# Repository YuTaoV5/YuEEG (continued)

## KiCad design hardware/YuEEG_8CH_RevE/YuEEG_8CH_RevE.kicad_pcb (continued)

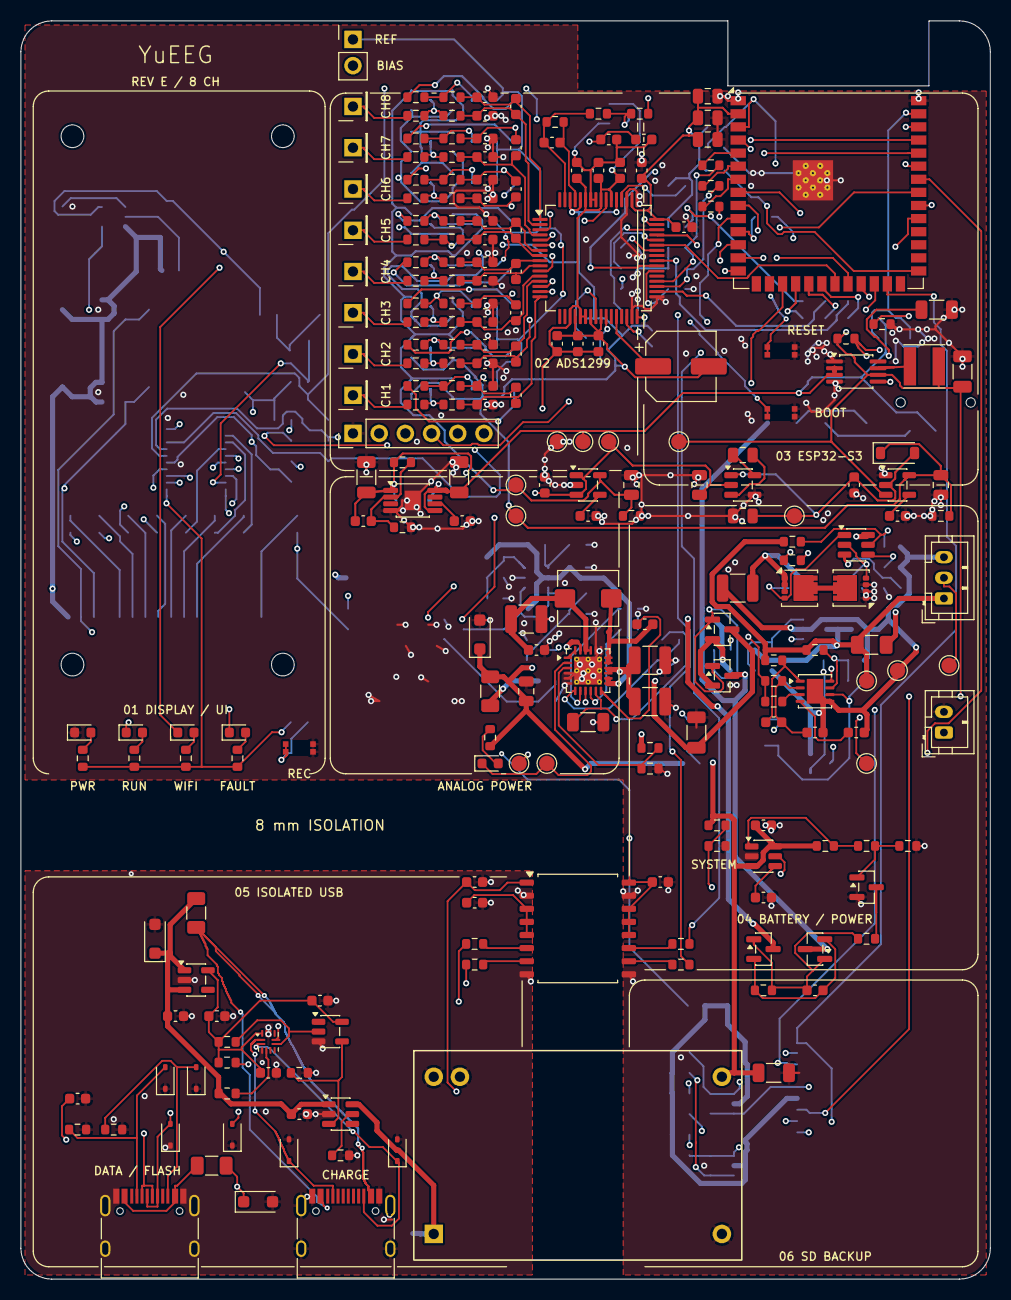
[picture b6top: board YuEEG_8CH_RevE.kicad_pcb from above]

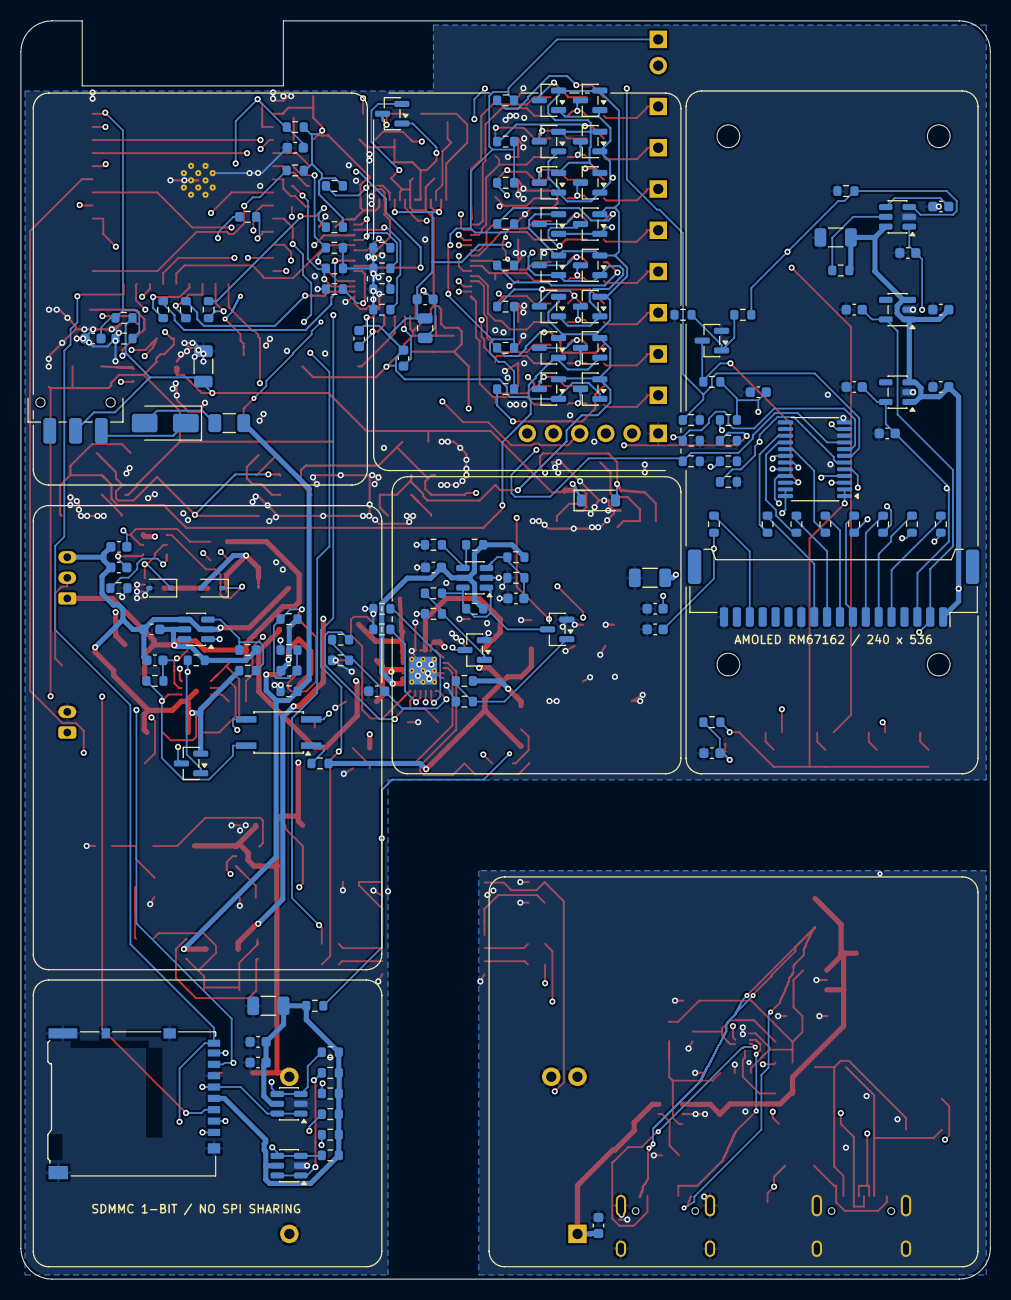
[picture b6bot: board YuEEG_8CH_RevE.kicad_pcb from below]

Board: 4 copper layers, 94.0 x 122.0 mm, 378 parts (145 on the bottom side), 224 nets.

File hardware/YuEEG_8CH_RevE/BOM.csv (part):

Reference,Value,Footprint,Sheet,Datasheet
U1,ADS1299PAG,Package_QFP:TQFP-64_10x10mm_P0.5mm,afe_core,https://www.ti.com/lit/ds/symlink/ads1299.pdf
R201,10k,Resistor_SMD:R_0603_1608Metric,afe_core,~
R202,10k,Resistor_SMD:R_0603_1608Metric,afe_core,~
R203,10k,Resistor_SMD:R_0603_1608Metric,afe_core,~
R204,10k,Resistor_SMD:R_0603_1608Metric,afe_core,~
R205,10k,Resistor_SMD:R_0603_1608Metric,afe_core,~
R206,10k,Resistor_SMD:R_0603_1608Metric,afe_core,~
R207,10k,Resistor_SMD:R_0603_1608Metric,afe_core,~
R208,10k,Resistor_SMD:R_0603_1608Metric,afe_core,~
R209,10k,Resistor_SMD:R_0603_1608Metric,afe_core,~
R210,1M 1%,Resistor_SMD:R_0603_1608Metric,afe_core,~
C201,1.5n C0G,Capacitor_SMD:C_0603_1608Metric,afe_core,~
R211,499k 1%,Resistor_SMD:R_0603_1608Metric,afe_core,~
R212,499k 1%,Resistor_SMD:R_0603_1608Metric,afe_core,~
J201,REF / BIAS,Connector_PinHeader_2.54mm:PinHeader_1x02_P2.54mm_Vertical,afe_core,~
C202,10u 10V X7R,Capacitor_SMD:C_0805_2012Metric,afe_core,~
C203,100n 10V,Capacitor_SMD:C_0603_1608Metric,afe_core,~
C210,1u 10V X7R,Capacitor_SMD:C_0603_1608Metric,afe_core,~
C211,1u 10V X7R,Capacitor_SMD:C_0603_1608Metric,afe_core,~
C212,1u 10V X7R,Capacitor_SMD:C_0603_1608Metric,afe_core,~
C213,1u 10V X7R,Capacitor_SMD:C_0603_1608Metric,afe_core,~
C214,1u 10V X7R,Capacitor_SMD:C_0603_1608Metric,afe_core,~
C215,1u 10V X7R,Capacitor_SMD:C_0603_1608Metric,afe_core,~
C216,1u 10V X7R,Capacitor_SMD:C_0603_1608Metric,afe_core,~
C217,1u 10V X7R,Capacitor_SMD:C_0603_1608Metric,afe_core,~
C220,100u 10V,Capacitor_SMD:CP_Elec_6.3x7.7,afe_core,~
C221,1u 10V,Capacitor_SMD:C_0603_1608Metric,afe_core,~
C222,1u 10V,Capacitor_SMD:C_0603_1608Metric,afe_core,~
C223,100n 10V,Capacitor_SMD:C_0603_1608Metric,afe_core,~
C224,1u 10V,Capacitor_SMD:C_0603_1608Metric,afe_core,~
D801,BAV199 BIAS CLAMP,Package_TO_SOT_SMD:SOT-23,afe_core,https://assets.nexperia.com/documents/data-sheet/BAV199.pdf
U1001,TPS22918DBVR AMOLED POWER,Package_TO_SOT_SMD:SOT-23-6,amoled_ui,https://www.ti.com/lit/ds/symlink/tps22918.pdf
R1001,100k,Resistor_SMD:R_0603_1608Metric,amoled_ui,~
C1001,1n 25V,Capacitor_SMD:C_0603_1608Metric,amoled_ui,~
R1003,1k,Resistor_SMD:R_0603_1608Metric,amoled_ui,~
C1002,22u 10V X7R,Capacitor_SMD:C_1206_3216Metric,amoled_ui,~
C1003,100n 10V,Capacitor_SMD:C_0603_1608Metric,amoled_ui,~
U1002,TPS7A2028PDBVR,Package_TO_SOT_SMD:SOT-23-5,amoled_ui,https://www.ti.com/lit/ds/symlink/tps7a20.pdf
C1004,1u 10V,Capacitor_SMD:C_0603_1608Metric,amoled_ui,~
C1005,4.7u 10V,Capacitor_SMD:C_0603_1608Metric,amoled_ui,~
U1003,TPS7A2018PDBVR,Package_TO_SOT_SMD:SOT-23-5,amoled_ui,https://www.ti.com/lit/ds/symlink/tps7a20.pdf
C1006,1u 10V,Capacitor_SMD:C_0603_1608Metric,amoled_ui,~
C1007,4.7u 10V,Capacitor_SMD:C_0603_1608Metric,amoled_ui,~
U1004,SN74AXC8T245PWR / 3V3 -> 1V8,Package_SO:TSSOP-24_4.4x7.8mm_P0.65mm,amoled_ui,https://www.ti.com/lit/ds/symlink/sn74axc8t245.pdf
C1008,100n 10V,Capacitor_SMD:C_0603_1608Metric,amoled_ui,~
C1009,100n 10V,Capacitor_SMD:C_0603_1608Metric,amoled_ui,~
Q1001,MMBT3904 OE ENABLE,Package_TO_SOT_SMD:SOT-23,amoled_ui,https://www.onsemi.com/pdf/datasheet/pzt3904-d.pdf
R1002,10k,Resistor_SMD:R_0603_1608Metric,amoled_ui,~
R1004,100k,Resistor_SMD:R_0603_1608Metric,amoled_ui,~
R1005,1M,Resistor_SMD:R_0603_1608Metric,amoled_ui,~
R1021,22R,Resistor_SMD:R_0603_1608Metric,amoled_ui,~
R1022,22R,Resistor_SMD:R_0603_1608Metric,amoled_ui,~
R1023,22R,Resistor_SMD:R_0603_1608Metric,amoled_ui,~
R1024,22R,Resistor_SMD:R_0603_1608Metric,amoled_ui,~
R1025,22R,Resistor_SMD:R_0603_1608Metric,amoled_ui,~
R1026,22R,Resistor_SMD:R_0603_1608Metric,amoled_ui,~
R1027,22R,Resistor_SMD:R_0603_1608Metric,amoled_ui,~
J1001,DO0200PFS12 18-PIN HARNESS,Connector_Molex:Molex_Panelmate_53780-1870_1x18-1MP_P1.25mm_Horizontal,amoled_ui,~
R1006,10k,Resistor_SMD:R_0603_1608Metric,amoled_ui,~
R1031,47k,Resistor_SMD:R_0603_1608Metric,amoled_ui,~
R1032,47k,Resistor_SMD:R_0603_1608Metric,amoled_ui,~
R1033,47k,Resistor_SMD:R_0603_1608Metric,amoled_ui,~
R1034,47k,Resistor_SMD:R_0603_1608Metric,amoled_ui,~
R1035,47k,Resistor_SMD:R_0603_1608Metric,amoled_ui,~
R1036,47k,Resistor_SMD:R_0603_1608Metric,amoled_ui,~
R1037,47k,Resistor_SMD:R_0603_1608Metric,amoled_ui,~
C1010,22u 10V X7R,Capacitor_SMD:C_1206_3216Metric,amoled_ui,~
C1011,1u 10V,Capacitor_SMD:C_0603_1608Metric,amoled_ui,~
C1012,100n 10V,Capacitor_SMD:C_0603_1608Metric,amoled_ui,~
U603,BQ29209DRBR,Package_SON:VSON-8-1EP_3x3mm_P0.65mm_EP1.6x2.4mm,battery_balance,https://www.ti.com/lit/ds/symlink/bq29209.pdf
R630,160R 1%,Resistor_SMD:R_0603_1608Metric,battery_balance,~
R631,260R 1%,Resistor_SMD:R_0603_1608Metric,battery_balance,~
R632,100R 1%,Resistor_SMD:R_0603_1608Metric,battery_balance,~
R633,100R 1%,Resistor_SMD:R_0603_1608Metric,battery_balance,~
C630,100n 16V,Capacitor_SMD:C_0603_1608Metric,battery_balance,~
C631,100n 16V,Capacitor_SMD:C_0603_1608Metric,battery_balance,~
C632,100n 16V,Capacitor_SMD:C_0603_1608Metric,battery_balance,~
C633,330n 16V,Capacitor_SMD:C_0603_1608Metric,battery_balance,~
R634,330k,Resistor_SMD:R_0603_1608Metric,battery_balance,~
U605,TPS3700DDCR BAL UV,Package_TO_SOT_SMD:SOT-23-6,battery_balance,https://www.ti.com/lit/ds/symlink/tps3700.pdf
R660,1.81M 0.1%,Resistor_SMD:R_0603_1608Metric,battery_balance,~
R661,100k 0.1%,Resistor_SMD:R_0603_1608Metric,battery_balance,~
R662,1M,Resistor_SMD:R_0603_1608Metric,battery_balance,~
C660,100n 16V,Capacitor_SMD:C_0603_1608Metric,battery_balance,~
U606,LTV-356T VALID USB,Package_SO:SO-4_4.4x3.6mm_P2.54mm,battery_balance,http://optoelectronics.liteon.com/upload/download/DS70-2001-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
R663,2.2k,Resistor_SMD:R_0603_1608Metric,battery_balance,~
Q607,2N7002 RAW UV GATE,Package_TO_SOT_SMD:SOT-23,battery_balance,https://www.onsemi.com/pub/Collateral/NDS7002A-D.PDF
TP601,RAW_BPLUS,TestPoint:TestPoint_Pad_D1.5mm,battery_balance,~
TP602,RAW_MID,TestPoint:TestPoint_Pad_D1.5mm,battery_balance,~
TP603,RAW_BMINUS,TestPoint:TestPoint_Pad_D1.5mm,battery_balance,~
TP604,BAL_OV_ALARM,TestPoint:TestPoint_Pad_D1.5mm,battery_balance,~
TP605,CHG_PG,TestPoint:TestPoint_Pad_D1.5mm,battery_balance,~
TP606,CHG_STAT,TestPoint:TestPoint_Pad_D1.5mm,battery_balance,~
J601,USB-C DATA / FLASH - ISOLATED,Connector_USB:USB_C_Receptacle_HRO_TYPE-C-31-M-12,battery_charger,https://www.usb.org/sites/default/files/documents/usb_type-c.zip
R601,10k 1%,Resistor_SMD:R_0603_1608Metric,battery_charger,~
R602,10k 1%,Resistor_SMD:R_0603_1608Metric,battery_charger,~
F602,1A hold PTC,Fuse:Fuse_1206_3216Metric,battery_charger,~
D601,SMF5.0A,Diode_SMD:D_SOD-123F,battery_charger,~
D602,PESD5V0U1BAF,Diode_SMD:D_SOD-323,battery_charger,https://assets.nexperia.com/documents/data-sheet/PESD5V0U1BA.pdf
D603,PESD5V0U1BAF,Diode_SMD:D_SOD-323,battery_charger,https://assets.nexperia.com/documents/data-sheet/PESD5V0U1BA.pdf
D604,PESD5V0S1BA,Diode_SMD:D_SOD-323,battery_charger,~
D605,PESD5V0S1BA,Diode_SMD:D_SOD-323,battery_charger,~
U601,BQ25886RGER,Package_DFN_QFN:Texas_RGE0024H_VQFN-24-1EP_4x4mm_P0.5mm_EP2.7x2.7mm_ThermalVias,battery_charger,http://www.ti.com/lit/ds/symlink/bq25886.pdf
C601,4.7u 16V X7R,Capacitor_SMD:C_0805_2012Metric,battery_charger,~
C602,47u 16V X7R,Capacitor_SMD:C_1210_3225Metric,battery_charger,~
C603,100n 16V,Capacitor_SMD:C_0603_1608Metric,battery_charger,~
C604,22u 16V X7R,Capacitor_SMD:C_1206_3216Metric,battery_charger,~
C605,47u 16V X7R,Capacitor_SMD:C_1210_3225Metric,battery_charger,~
C606,47u 16V X7R,Capacitor_SMD:C_1210_3225Metric,battery_charger,~
C607,22u 25V X7R,Capacitor_SMD:C_1206_3216Metric,battery_charger,~
C608,47n 25V X7R,Capacitor_SMD:C_0603_1608Metric,battery_charger,~
L601,1uH SRP5030T-1R0M / Isat11A,Inductor_SMD:L_Bourns_SRP5030T,battery_charger,~
R603,1.50k 1%,Resistor_SMD:R_0603_1608Metric,battery_charger,~
R604,1.14k 1%,Resistor_SMD:R_0603_1608Metric,battery_charger,~
R605,9.31k 0.1%,Resistor_SMD:R_0603_1608Metric,battery_charger,~
R606,365k 0.1%,Resistor_SMD:R_0603_1608Metric,battery_charger,~
J602,CELL NTC / 103AT-2 10k,Connector_JST:JST_PH_B2B-PH-K_1x02_P2.00mm_Vertical,battery_charger,~
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
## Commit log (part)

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2024-06-19 Part One
2024-06-19 Create README.md
    add readme
2024-11-10 V1.6
2024-11-11 update readme, change gui
2024-11-11 add paradigm
2024-11-11 change 3mf files
2024-11-11 update model
2024-11-13 add plot_only.py
2024-11-19 change 外壳.3mf
2025-02-25 update new ino file
2025-03-05 new update
2025-03-10 fix plot bug
2025-06-10 update new plot program
2025-08-24 normal update
2025-08-24 delate some log
2025-08-24 change structure
